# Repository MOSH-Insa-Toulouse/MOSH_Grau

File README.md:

# MOSH_Grau
# Projet capteur

## SOMMAIRE 
* 1 [Description du projet](#description)
* 2 [Shield](#paragraph2)
* 3 [Arduino](#paragraph3)
* 4 [APK](#paragraph4)  
* 5 [Banc de test](#paragraph5)
* 6 [Idées d'amélioration et de développement](#paragraph6)

   La plupart des iformations se trouvent dans la datasheet.

--------- 
## Description du projet 

Ce projet est réalisé dans le cadre de la formation en ingénierie physique de l'INSA Toulouse. Il vise à introduire le développement de technologies performantes, transportables et à moindre coût. 
Ce projet aborde de nombreuses notions : la physique des systèmes granulaires, l'électroniqe analogique, Arduino Uno, la réalisation d'un PCB, le développement d'APK, la conception d'un banc de test et la réalisation d'une datasheet.

*Objectif* : Développer une jauge de contrainte lowtech, carctérisée et documentée. 

*Description du capteur* : Le capteur est une feuille de papier sur laquelle est déposée une fine couche de graphite. Le graphite déposée peut être vu comme un film conducteur constitué de réseaux de percolation. La déformation du papier se répercute sur les réseaux de percolation et donc sur la conductivité du film de graphite. La déformation du papier est proportionnelle à la variation de conductivité du film de graphite[¹]. Afin d'avoir une mesure de meilleure qualité,et en raison des valeurs de résistance du capteur treès élevées, le signal est conditionné par un circuit analogique comprenant un amplificateur transimpédance et différents filtres. Un écran OLED piloté par un encodeur rotatoire permet d'étendre les fonctionnalités du capteur. Une application Android a également été développée pour faciliter l'utilisation du capteur, même si le capteur se suffit à lui même. L'application et le capteur communique via un module bluetooth. Le shield comprenant tous les composants électroniques s'enfiche sur une carte Arduino Uno.

*Livrables* : 

1. Shield : comprend un amplificateur transimpédance, différents étages de filtrage, un module bluetooth (HC-05), un écran OLED (SSD1306) et un encodeur rotatoire (KY-040). La résistance R2 peut être changée facilement afin d'adapter le gain de l'amplificateur en fonction de la résistance du capteur. 
2. Code Arduino : permet de piloter l'encodeur rotatoire et l'écran OLED. Un menu s'affiche à l'écran avec 3 fonctionnailités principales:
- choix de R2
- choix de l'affichage de différentes mesures en temps réel : soit la tension à la sortie de A0 (ADC sur 10 bits), soit la déformation longitudinale du capteur, ou bien la résistance du capteur. 
- Mesure de contrainte au niveau de la jauge de déformation en fonction du matériaux choisi.
- Calibration du capteur (sensibilité).

Gère les flux de données entre l'APK et le microcontrôleur via le module BT. Permet également d'effectuer les différents traitements de données, comme le calcul de la déformation longitudinale en fonction de la déflection ou encore le calcule de contrainte en fonction de la déformation et d'un certain matériau (module de Young). 

3. APK : Affichage en temps réel  de la tension à la sortie de A0 (ADC sur 10 bits) et tracé du graphe correspondant, affichage de la résistance du capteur, et affichage et modification de la valeur de R2. Un fonctionnalité permet de faire la moyenne des mesures sur 5 secondes. 

[¹]: https://www.nature.com/articles/srep03812

--------- 
## Banc de test 

### Description du banc de test ###

La solution choisie afin de tester et caractériser les capteurs est l'application d'une déflection en compression ou en traction. 

- Déflection en compression : on fixe le capteur au niveau de la partie la plus large, et on applique une déflection contrôlable et mesurable (par exemple avec une règle), perpendiculairement vers le haut (avec la couche de graphite sur la face supérieure du papier) et à l'extrèmité de la jauge pour qu'elle se replie sur elle-même. 
- Déflection en traction : idem qu'en compression mais avec une délection provoquée par une froce dirigée vers le bas (avec la couche de graphite sur la face supérieure du papier). Plus difficile à mettre en oeuvre pour des raisons pratiques, notamment pour mesurer la déflection correctement. On peut alors s'aider de poids que l'on suspend à l'extrémité de la jauge. 

 On mesure ainsi la variation de résistance relative en fonction de la déflection. En considérant notre capteur comme une poutre, avec de petites déformation nous pouvons alor remonter à la déformation logitudinale du capteur et calculer son facteur de jauge. Il est important que les prises de contact soient immobiles tout au long de la mesure pour ne pas fausser celle-ci. 
 Il faut également toucher le moins possible la couche de graphite du capteur pour ne pas biaiser les mesures.
 Pour effectuer nos mesures, noud avons moyenné chaque point sur 5 secondes à une fréquence dacquisition de 5Hz. L'incertitude de chaque mesure correspond à l'écart type de l'ensemble des échantillons correspondants à la mesure (voir APK).
 La défelction maximale appliquée est de 2 cm, au delà la déformation du capteur devient trop importante et il se peut que celui-ci se retrouve déformé de manière irréversible. 

**Paramètres étudiés :**

*Paramètres contrôlables :*

1. Type de papier : 
- Papier canson, 180 g/m², épaiseur : 0,21mm
- Feuille A4 de bureau standard, 80 g/m², épaisseur : 0,08mm,
- Fiche Bristol, 205 g/m², épaisseur : 0,22mm

2. Type de crayon : De 4H à 4B
3. Forme de la jauge, notamment la surface de la couche de graphite, la longueur du motif de graphite etc... 
4. Influence de la résistance nominale
5. Influence de R2

*Paramètres non contrôlables :*

1. Formation des réseaux de percolation
2. Epaisseur de la couche de graphite
3. Homogénéité de la couche de graphite

### Influence de R2 sur la mesure ###

La résistance R2 permet d'adapter le gain de l'amplificateur. Il permet notamment de déterminer la plage de résistance mesurable : 

###Idées d'amélioration et de développement 

- Réfléchir à un moyen de déposer le graphite de manière plus homogène
- Continuer à étudier les différents paramètre : dimensions de la jauge de graphite, dimensions du motif de graphite
- Réfléchir à une prise de contact plus appropriée, avec des électrodes fixes
- Continuer à prendre des mesures pour préciser ou réfuter la relation entre la résistance nominale et le facteur de jauge
- Faire les mesures en compression
- Automatiser le banc de test, en fixant tout simplement un fil au bout de la jauge, avec l'autre bout du fil accroché à un servomoteur. L'angle de rotation du servo-moteur est directement relié à la déflection de la jauge. 
- Optimiser le code de l'APK, et de l'Arduino, ajout de nouvelles fonctionnalités

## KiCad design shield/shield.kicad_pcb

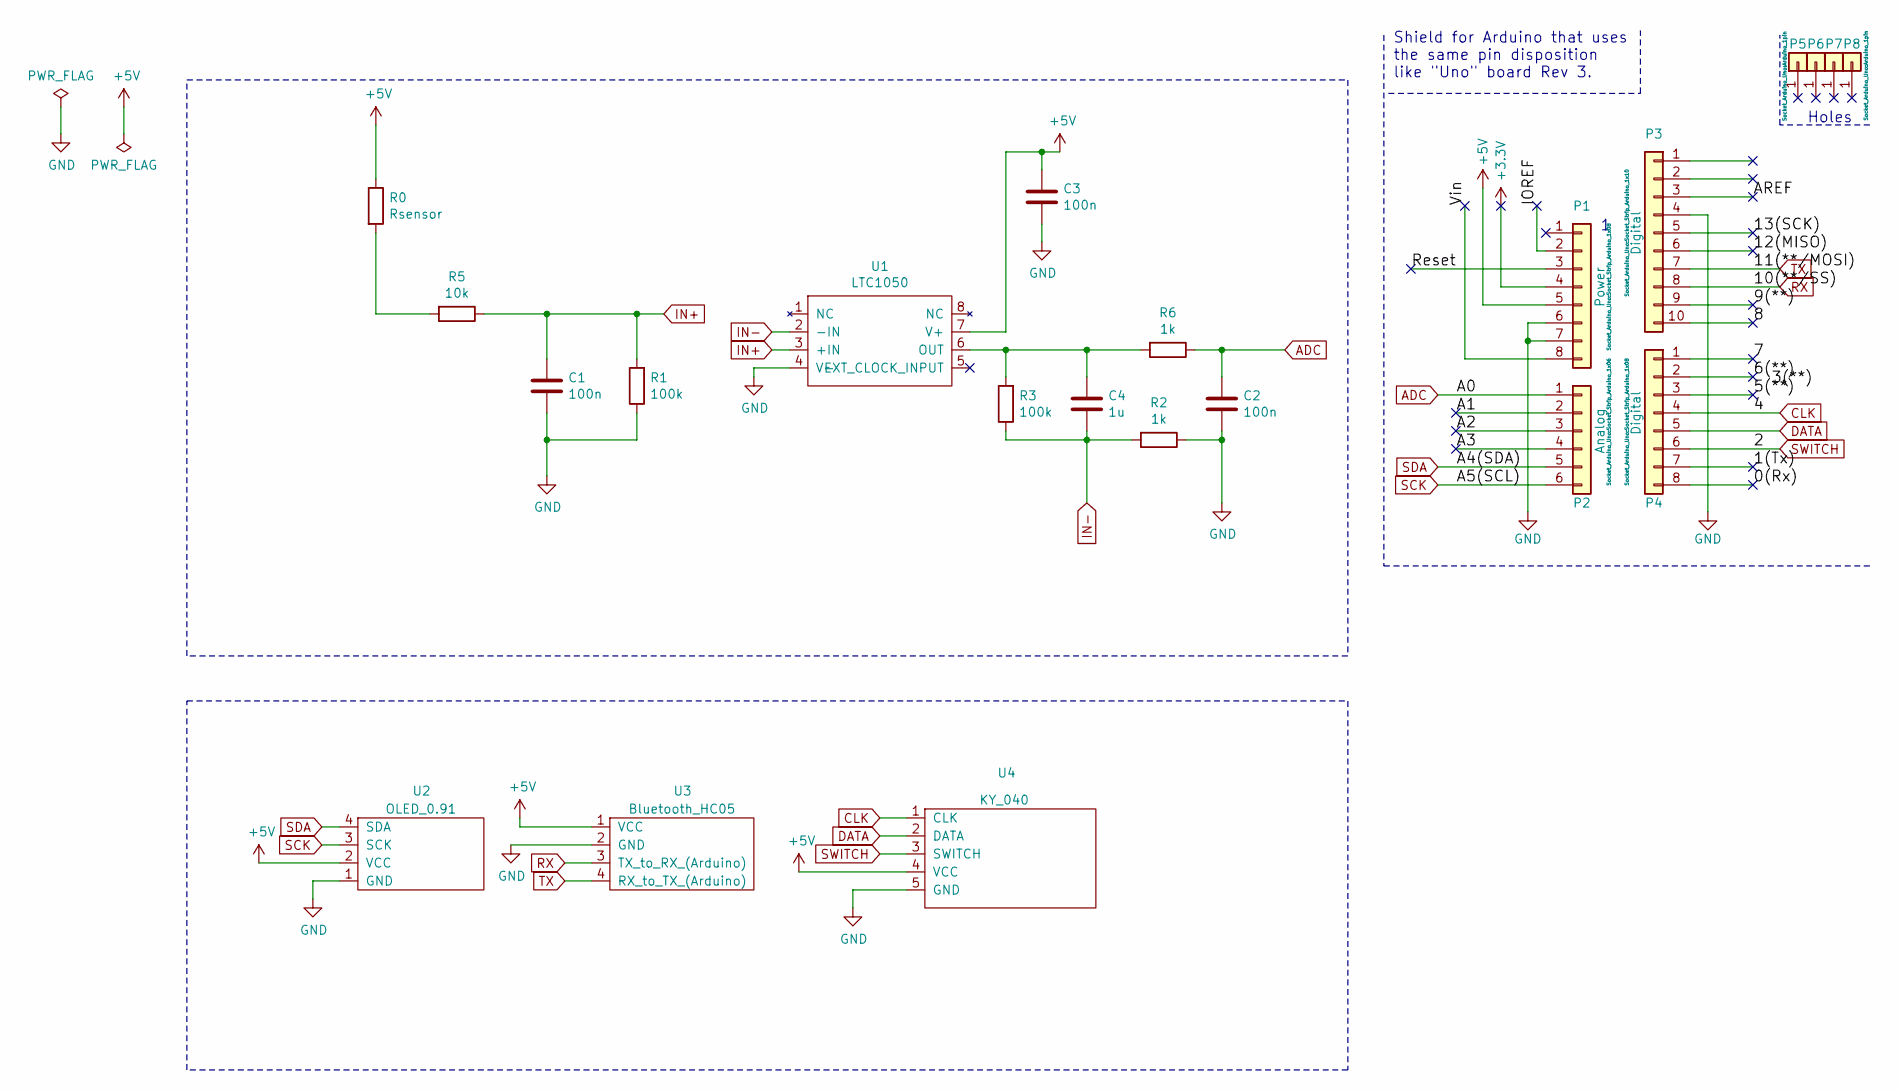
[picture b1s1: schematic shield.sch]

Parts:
C1, C2, C3: 100n; C_Disc_D5.1mm_W3.2mm_P5.00mm
C4: 1u; C_Disc_D5.1mm_W3.2mm_P5.00mm
P1: Power; Socket_Strip_Arduino_1x08
P2: Analog; Socket_Strip_Arduino_1x06
P3: Digital; Socket_Strip_Arduino_1x10
P4: Digital; Socket_Strip_Arduino_1x08
P5, P6, P7, P8: CONN_01X01; Arduino_1pin
R0: Rsensor; R_Axial_DIN0207_L6.3mm_D2.5mm_P10.16mm_Horizontal
R1, R3: 100k; R_Axial_DIN0207_L6.3mm_D2.5mm_P10.16mm_Horizontal
R2, R6: 1k; R_Axial_DIN0207_L6.3mm_D2.5mm_P10.16mm_Horizontal
R5: 10k; R_Axial_DIN0207_L6.3mm_D2.5mm_P10.16mm_Horizontal
U1: LTC1050; emp_LTC_1050
U2: OLED_0.91; emp_bluetooth_HC05
U3: Bluetooth_HC05; emp_bluetooth_HC05
U4: KY_040

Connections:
+3V3: P1.4
+5V: C3.1, P1.5, R0.1, U1.7 (V+), U2.2 (VCC), U3.1 (VCC), U4.4 (VCC)
/0(Rx): P4.8
/1(Tx): P4.7
/5(**): P4.3
/6(**): P4.2
/7: P4.1
/8: P3.10
/9(**): P3.9
/12(MISO): P3.6
/13(SCK): P3.5
/A1: P2.2
/A2: P2.3
/A3: P2.4
/AREF: P3.3
/IOREF: P1.2
/Reset: P1.3
/Vin: P1.8
ADC: C2.1, P2.1, R6.1
CLK: P4.4, U4.1 (CLK)
DATA: P4.5, U4.2 (DATA)
GND: C1.2, C2.2, C3.2, P1.6, P1.7, P3.4, R1.1, R2.1, U1.4 (V-), U2.1 (GND), U3.2 (GND), U4.5 (GND)
IN+: C1.1, R1.2, R5.1, U1.3 (+IN)
IN-: C4.2, R2.2, R3.1, U1.2 (-IN)
unnamed: C4.1, R3.2, R6.2, U1.6 (OUT)
unnamed: R0.2, R5.2
RX: P3.8, U3.3 (TX_to_RX_(Arduino))
SCK: P2.6, U2.3 (SCK)
SDA: P2.5, U2.4 (SDA)
SWITCH: P4.6, U4.3 (SWITCH)
TX: P3.7, U3.4 (RX_to_TX_(Arduino))

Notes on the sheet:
Holes
Shield for Arduino that uses the same pin disposition like "Uno" board Rev 3.

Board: 2 copper layers, 22 parts (0 on the bottom side), 14 nets, no tracks yet.

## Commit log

2021-04-02 ajout du dossier Projet_Kicad_Victor
2021-04-02 commit 02/04/21 test
2021-04-05 premier commit du dossier shield
2021-04-08 premier commit code_arduino
2021-04-10 commit organisation des fichiers
2021-04-10 dev affichage OLED arduino
2021-04-12 ajout des menus
2021-04-28 commit résultats
2021-04-28 commit rapport résultats
2021-04-30 commit res
2021-04-30 commit arduino
2021-05-02 commit code arduino, ajout fonctionnalités 02/05
2021-05-03 commit datasheet
2021-05-03 03/05
2021-05-05 commit APK
